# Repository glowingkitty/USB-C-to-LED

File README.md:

# USB-C to LED

A PCB for connecting LED strips easily via USB-C.

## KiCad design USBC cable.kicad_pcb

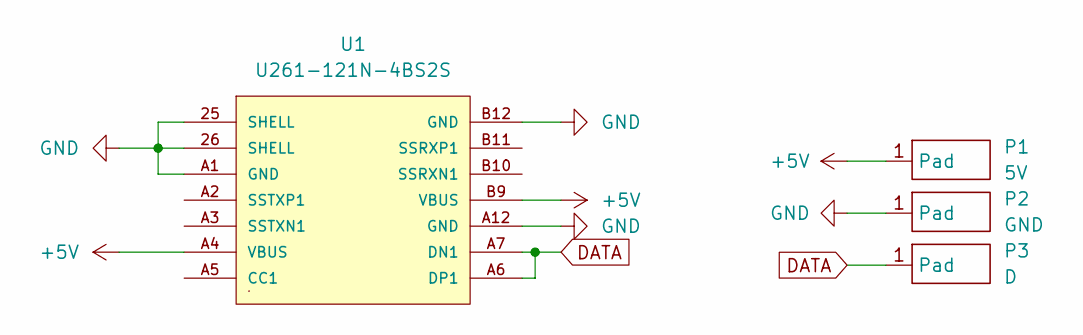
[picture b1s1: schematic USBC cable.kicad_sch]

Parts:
P1: 5V; CopperField
P2: GND; CopperField
P3: D; CopperField
U1: U261-121N-4BS2S; Mfr. Part # U261-121N-4BS2S; LCSC Part # C2879827

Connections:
+5V: P1.1 (Pad), U1.A4 (VBUS), U1.B9 (VBUS)
DATA: P3.1 (Pad), U1.A6 (DP1), U1.A7 (DN1)
GND: P2.1 (Pad), U1.25 (SHELL), U1.26 (SHELL), U1.A1 (GND), U1.A12 (GND), U1.B12 (GND)

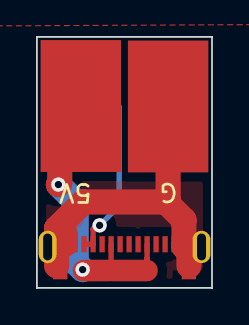
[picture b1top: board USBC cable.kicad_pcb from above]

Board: 2 copper layers, 9.7 x 13.9 mm, 4 parts (1 on the bottom side), 3 nets.

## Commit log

2022-02-01 added pcb files for v1
2022-02-01 replaced small pins with large pads
